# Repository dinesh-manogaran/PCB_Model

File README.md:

View this project on [CADLAB.io](https://cadlab.io/project/29157). 

# PCB_Model

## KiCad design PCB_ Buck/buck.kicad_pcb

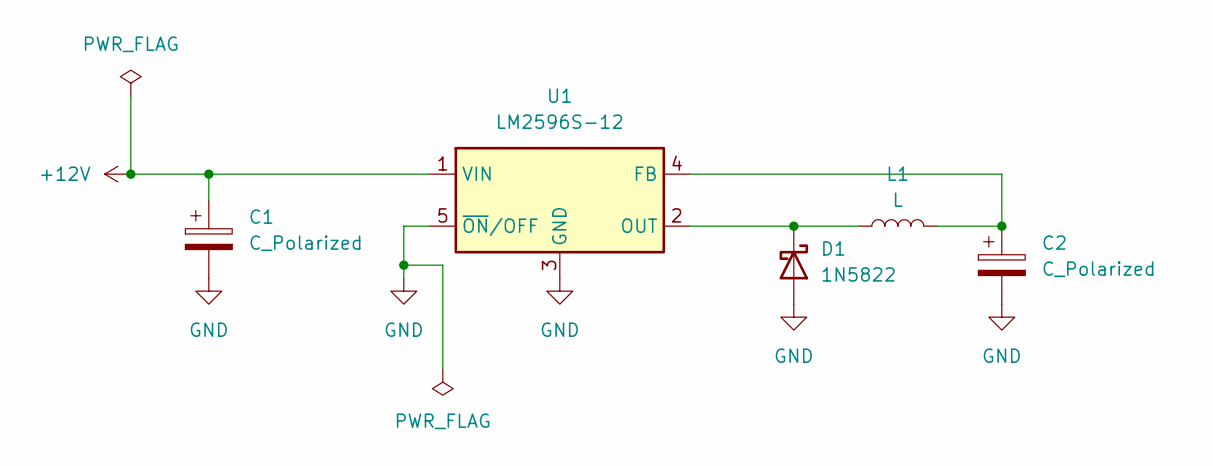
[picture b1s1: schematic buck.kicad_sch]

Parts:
C1, C2: C_Polarized; CP_Elec_5x3
D1: 1N5822; D_3220_8050Metric_Pad2.65x5.15mm_HandSolder
L1: L; L_0805_2012Metric_Pad1.15x1.40mm_HandSolder
U1: LM2596S-12; TO-263-5_TabPin3

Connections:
+12V: C1.1, U1.1 (VIN)
GND: C1.2, C2.2, D1.2 (A), U1.3 (GND), U1.5 (~ON/OFF)
unnamed: D1.1 (K), L1.1, U1.2 (OUT)
unnamed: C2.1, L1.2, U1.4 (FB)

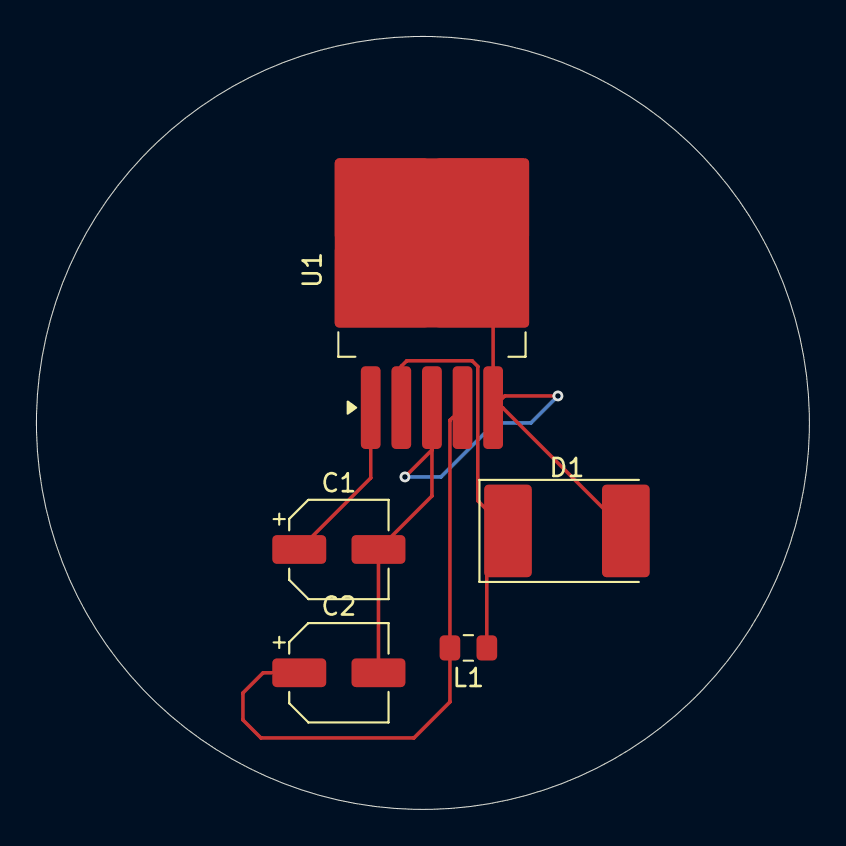
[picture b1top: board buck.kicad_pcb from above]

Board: 2 copper layers, 42.9 x 42.9 mm, 5 parts (0 on the bottom side), 4 nets.

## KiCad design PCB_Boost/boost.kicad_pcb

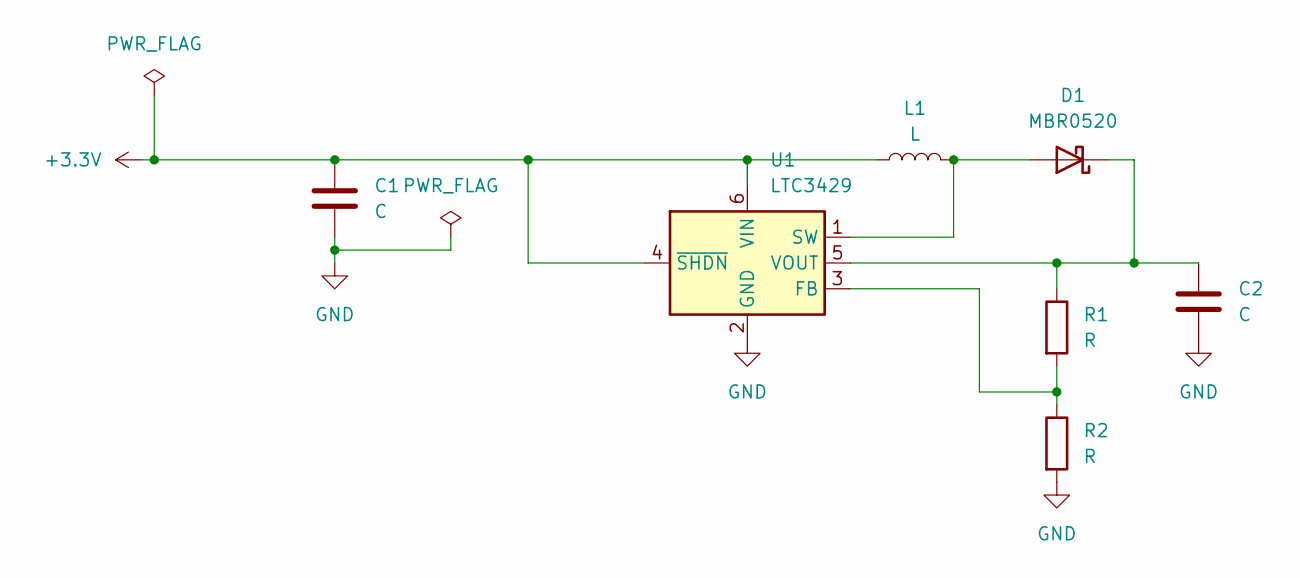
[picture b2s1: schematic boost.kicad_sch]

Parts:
C1, C2: C; CP_Axial_L11.0mm_D6.0mm_P18.00mm_Horizontal
D1: MBR0520; D_SOD-123
L1: L; L_Axial_L5.3mm_D2.2mm_P7.62mm_Horizontal_Vishay_IM-1
R1, R2: R; R_Axial_DIN0309_L9.0mm_D3.2mm_P20.32mm_Horizontal
U1: LTC3429; TSOT-23-6

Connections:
+3.3V: C1.1, L1.1, U1.4 (~SHDN), U1.6 (VIN)
GND: C1.2, C2.2, R2.2, U1.2 (GND)
unnamed: D1.2 (A), L1.2, U1.1 (SW)
unnamed: C2.1, D1.1 (K), R1.1, U1.5 (VOUT)
unnamed: R1.2, R2.1, U1.3 (FB)

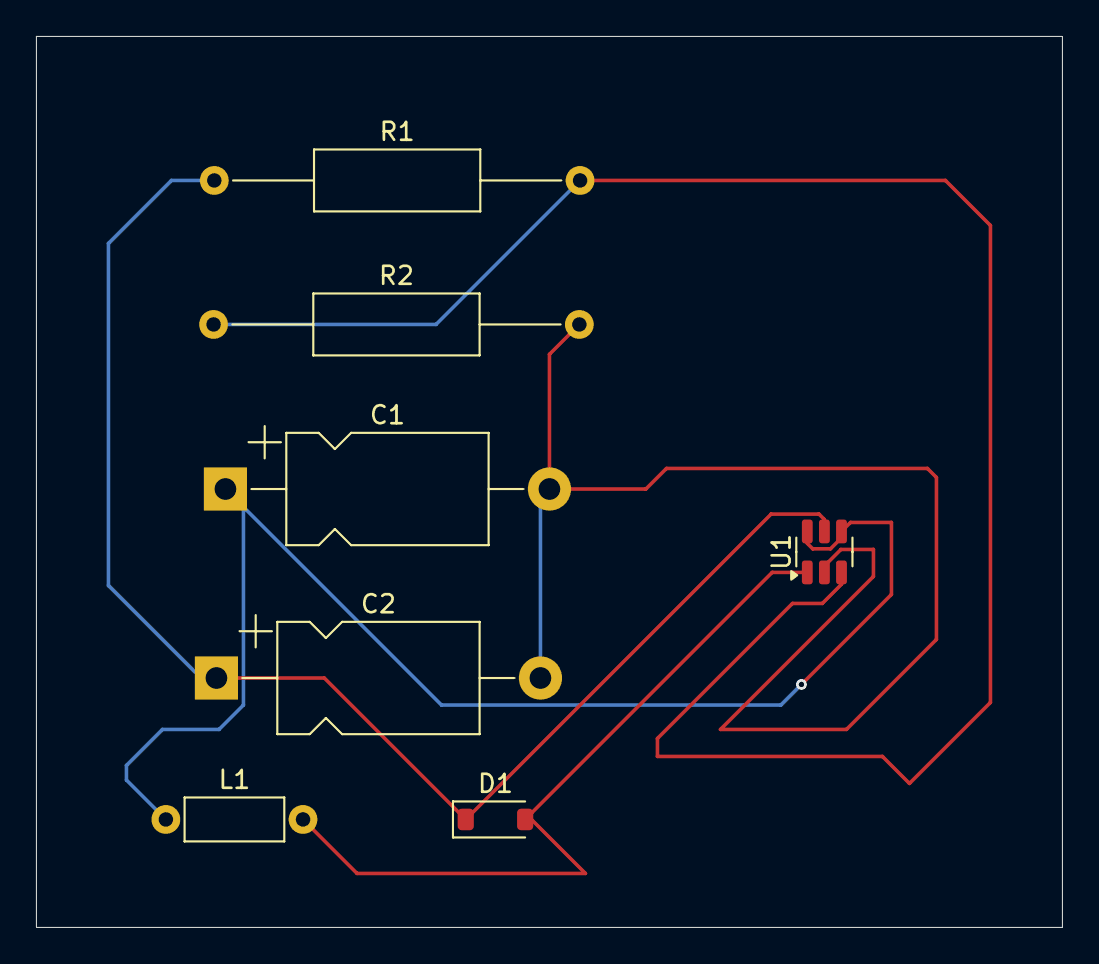
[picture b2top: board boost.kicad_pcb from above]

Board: 2 copper layers, 57.0 x 49.5 mm, 7 parts (0 on the bottom side), 5 nets.

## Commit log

2025-03-24 Design
2025-04-03 Backlink to CADLAB.io has been added.
